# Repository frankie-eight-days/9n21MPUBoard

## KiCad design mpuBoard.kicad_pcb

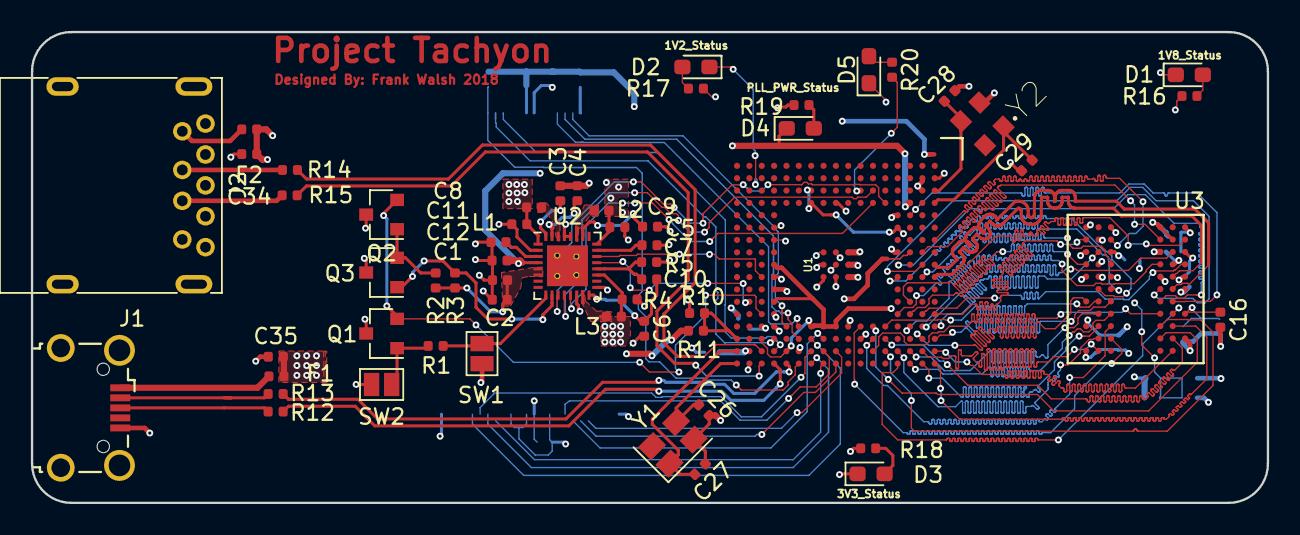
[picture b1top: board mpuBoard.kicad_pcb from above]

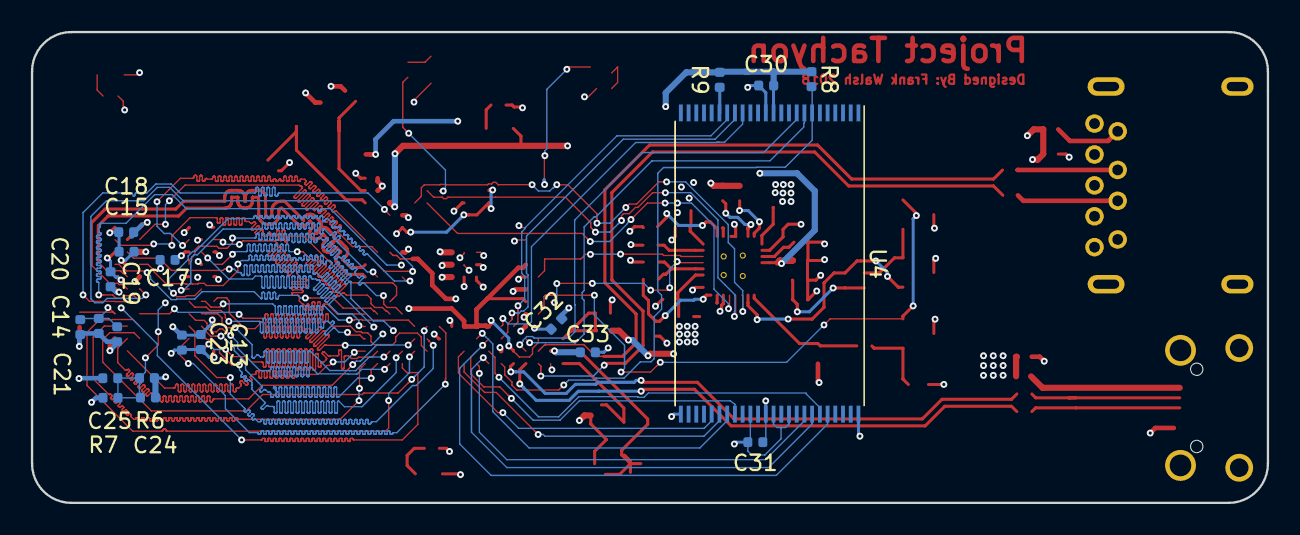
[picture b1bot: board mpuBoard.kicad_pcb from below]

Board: 4 copper layers, 80.0 x 30.5 mm, 77 parts (20 on the bottom side), 94 nets.

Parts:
C1, C2, C4, C5, C6, C11, C12, C34: 4.7u; C_0402_1005Metric
C3, C13, C14, C15, C16, C17, C18, C19, C20, C21, C23, C24, C25, C32, C33: 100n; C_0402_1005Metric
C7, C35: C_Small; C_0402_1005Metric
C8, C9, C10: 20u; C_0402_1005Metric
C26, C27: 9p; C_0402_1005Metric
C28, C29: 18p; C_0402_1005Metric
C30, C31: 1u; C_0402_1005Metric
D1, D2, D3, D4, D5: LED; LED_0603_1608Metric_Pad1.05x0.95mm_HandSolder
F1, F2: 500mA, 5V; Fuse_0402_1005Metric
J1: USB_B_Micro; USB_Micro-B_Wuerth_629105150521_CircularHoles
J2: USB_A; USB3_A_Molex_48393-001
L1, L2, L3: 2.2u; L_0402_1005Metric
Q1, Q2, Q3: bss138; SOT-23
R1, R4, R5, R8, R9: 4.7k; R_0402_1005Metric
R2: 47k; R_0402_1005Metric
R3: 100k; R_0402_1005Metric
R6, R7, R16, R17, R18, R19: R; R_0402_1005Metric
R10, R11: 4.7K; R_0402_1005Metric
R12, R13, R14, R15: 22; R_0402_1005Metric
R20: 10k; R_0402_1005Metric
SW1, SW2: SW_Push; SolderJumper-2_P1.3mm_Open_Pad1.0x1.5mm
U1: AT91SAM9N12; BGA217
U2: ACT8865; QFN-32-1EP_4x4mm_P0.4mm_EP2.65x2.65mm
U3: as4c128m8d2-25bin
U4: S34ML08G201TFI; TSOP-I-48_18.4x12mm_P0.5mm
Y1: 16MHz; Crystal_SMD_SeikoEpson_FA238-4Pin_3.2x2.5mm
Y2: 32.768kHz; OSCSC320X250X100N

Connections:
+1V2: C9.1, D2.1, L2.2, U1.C8, U1.G15, U1.J4, U1.P10, U2.24
+1V8: C8.1, C13.1, C14.1, C15.1, C16.1, C17.1, C18.1, C19.1, C20.1, C21.1, C23.1, C24.1, D1.1, L1.2, R6.1, U1.H8, U1.H9, U1.H10, U2.1, U3.A1, U3.A9, U3.C1, U3.C3, U3.C7, U3.C9, U3.E1, U3.E9, U3.H9, U3.L1
+3V3: C10.1, C30.1, C31.1, D3.1, L3.2, R8.1, R9.1, R10.1, U1.A2, U1.D6, U1.J14, U1.K14, U1.L3, U1.L4, U1.L14, U1.N16, U1.P9, U1.P12, U1.R15, U2.19, U4.12, U4.34, U4.37, U4.39
+5V: C1.1, C2.1, C4.2, C5.2, C6.1, C34.1, C35.1, F1.1, F2.1, R2.1, R3.1, R4.1, U2.5, U2.6, U2.16, U2.26, U2.31
/memory/a0: U1.D17, U3.H8
/memory/a1: U1.C17, U3.H3
/memory/a2: U1.F16, U3.H7
/memory/a3: U1.B17, U3.J2
/memory/a4: U1.A17, U3.J8
/memory/a5: U1.F15, U3.J3
/memory/a6: U1.E16, U3.J7
/memory/a7: U1.D16, U3.K2
/memory/a8: U1.E15, U3.K8
/memory/a9: U1.G14, U3.K3
/memory/a10: U1.C16, U3.H2
/memory/a11: U1.F14, U3.K7
/memory/a12: U1.B16, U3.L2
/memory/a13: U1.A16, U3.L8
/memory/d0: U1.B14, U3.C8
/memory/d1: U1.A14, U3.C2
/memory/d2: U1.C14, U3.D7
/memory/d3: U1.D13, U3.D3
/memory/d4: U1.C13, U3.D1
/memory/d5: U1.B13, U3.D9
/memory/d6: U1.A13, U3.B1
/memory/d7: U1.C12, U3.B9
/memory/ramclk_N: U1.A9, U3.F8
/memory/ramclk_P: U1.A10, U3.E8
/memory/ramsel0: U1.C5, U3.G8
/memory/ramsel1: U1.B9, U3.F7
/memory/ramsel2: U1.D9, U3.G7
/memory/ramsel3: U1.B10, U3.F3
/memory/ramsel4: U1.D10, U3.F2
/memory/ramsel5: U1.B15, U3.G1
/memory/ramsel6: U1.E14, U3.G2
/memory/ramsel7: U1.A15, U3.G3
/memory/ramsel8: U1.B8, U3.B7
/memory/ramsel9: U1.A7, U3.B3
/mpu/D+: J1.3, R12.1
/mpu/D-: J1.2, R13.1
/mpu/actGPIO0: U1.E4, U2.11
/mpu/actGPIO1: U1.F3, U2.12
/mpu/actGPIO2: U1.F4, U2.13
/mpu/actSPI0: U1.R10, U2.22
/mpu/actSPI1: U1.T12, U2.21
/mpu/flashCTL0: U1.M14, U4.16
/mpu/flashCTL1: U1.M15, U4.17
/mpu/flashCTL2: U1.N14, U4.18
/mpu/flashCTL4: R8.2, U1.M17, U4.7
/mpu/flashCTL5: U1.P15, U4.8
/mpu/flashCTL6: U1.P16, U4.9
/mpu/flashData0: U1.L15, U4.44
/mpu/flashData1: U1.L16, U4.43
/mpu/flashData2: U1.L17, U4.42
/mpu/flashData3: U1.K17, U4.41
/mpu/flashData4: U1.K16, U4.32
/mpu/flashData5: U1.K15, U4.31
/mpu/flashData6: U1.J17, U4.30
/mpu/flashData7: U1.J16, U4.29
/mpu/fullD+: R15.1, U1.R17
/mpu/fullD-: R14.1, U1.R16
/mpu/microD+: R12.2, U1.P17
/mpu/microD-: R13.2, U1.N17
/mpu/mpu_shutdown: Q1.2, Q2.2, U1.R13
/nandFlash/flashCTL3: R9.2, U4.19
/power/PWRHLD: Q3.1, R3.2, U2.10
/power/sw1: L1.1, U2.30
/power/sw2: L2.1, U2.27
/power/sw3: L3.1, U2.15
/power/vddref: C7.1, U2.23
/power/vsel: R4.2, R5.1, U2.20
GND: C1.2, C2.2, C3.1, C4.1, C5.1, C6.2, C7.2, C8.2, C9.2, C10.2, C11.2, C12.2, C13.2, C14.2, C15.2, C16.2, C17.2, C18.2, C19.2, C20.2, C21.2, C23.2, C25.2, C26.1, C27.1, C28.1, C29.1, C30.2, C31.2, C32.2, C33.2, C34.2, C35.2, D5.1, J1.5, J1.6, J2.4, J2.5, Q1.3, Q2.3, Q3.3, R5.2, R7.2, R11.2, R16.2, R17.2, R18.2, R19.2, SW1.1, SW2.1, U1.B2, U1.B3, U1.D5, U1.D8, U1.H14, U1.J8, U1.J9, U1.J10, U1.K8, U1.K9, U1.K10, U1.M16, U1.P6, U1.P7, U1.P11, U1.P13, U1.P14, U1.T17, U2.2, U2.14, U2.17, U2.28, U2.29, U2.33, U3.A3, U3.A7, U3.B2, U3.B8, U3.D2, U3.D8, U3.E3, U3.E7, U3.F9, U3.J1, U3.K9, U4.13, U4.25, U4.36, U4.48, Y1.2, Y2.2
unnamed: C3.2, U2.32
unnamed: C24.2, C25.1, R6.2, R7.1, U3.E2
unnamed: C26.2, U1.U17, Y1.3
unnamed: C27.2, U1.U16, Y1.1
unnamed: C28.2, U1.A3, Y2.3
unnamed: C29.2, U1.A4, Y2.1
unnamed: D1.2, R16.1
unnamed: D2.2, R17.1
unnamed: D3.2, R18.1
unnamed: D4.2, R19.1
unnamed: D5.2, R20.1
unnamed: F1.2, J1.1
unnamed: F2.2, J2.1
unnamed: J2.2, R14.2
unnamed: J2.3, R15.2
unnamed: Q1.1, R1.2, SW2.2
unnamed: Q2.1, Q3.2, R2.2
unnamed: R1.1, SW1.2, U2.9
unnamed: R10.2, R11.1, U1.U15
unnamed: R20.2, U1.G3
out4: C11.1, U2.3
out5: C12.1, C32.1, C33.1, D4.1, U1.C4, U1.R14, U1.T16, U2.4

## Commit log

2018-10-14 schematic done. layout next
2018-10-24 Ordered boards
